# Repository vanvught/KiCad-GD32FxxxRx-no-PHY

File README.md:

[PayPal.Me Donate](https://paypal.me/AvanVught?locale.x=nl_NL)
-----------

# KiCad GD32F103R GD32F107R GD32F207R GD32F303R GD32F407R development board

This board can be used with the `GD32F103Rx`,  `GD32F303Rx` and the `GD32F107Rx` , `GD32F207Rx`, `GD32F407Rx` (Ethernet) MCU's. 

Please note that the crystal for the `GD32F107Rx`, `GD32F207Rx` and the `GD32F407Rx` is `25MHz` and the crystal for the `GD32F103Rx` and the  `GD32F303Rx` is `8MHz`.

The 2x13 header is pin compatible with the Orange Pi Zero and Raspberry Pi boards. 

Note: The BOM is for the GD32F407RE.
ToDo: Add information for other supported MCU's.

Details -> [https://www.gd32-dmx.org/dev-board.html](https://www.gd32-dmx.org/dev-board.html)

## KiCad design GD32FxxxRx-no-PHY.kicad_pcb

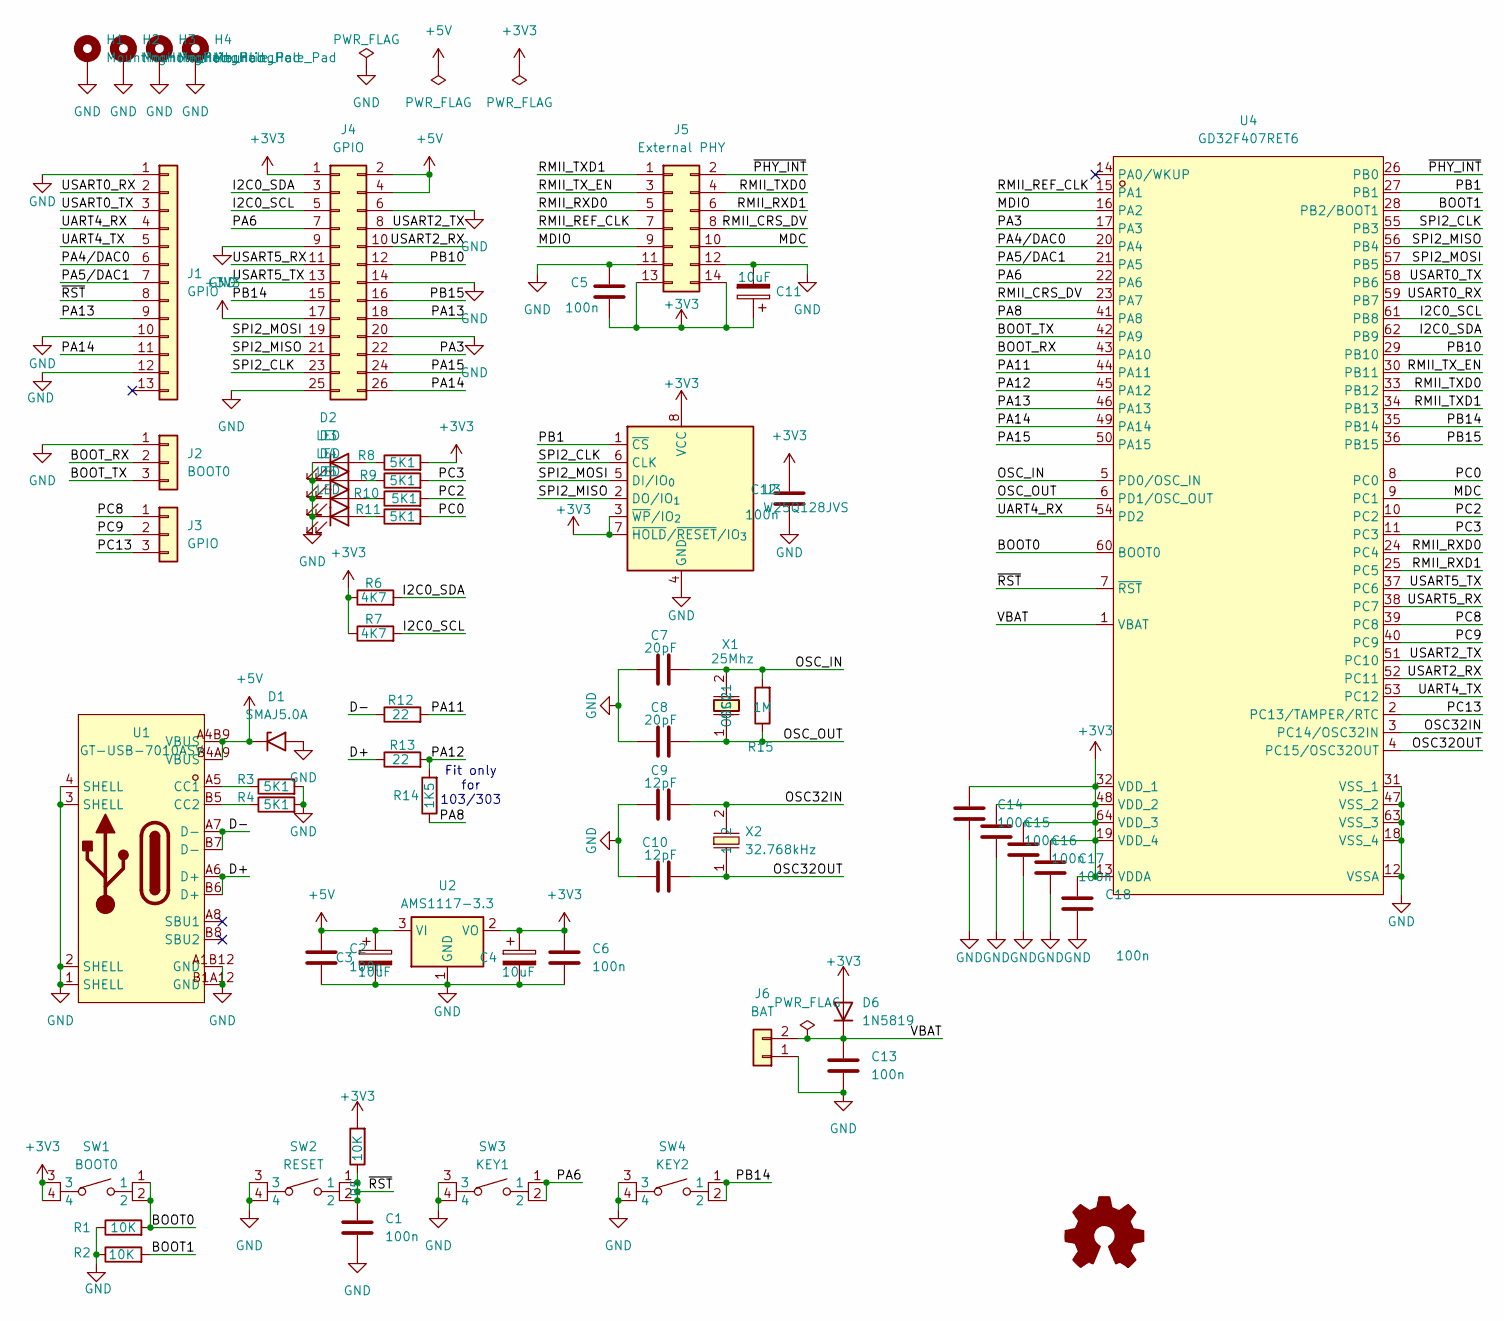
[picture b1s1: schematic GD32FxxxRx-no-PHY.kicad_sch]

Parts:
C1, C2, C5, C6, C12, C13, C14, C15, C16, C17, C18: 100n; C_0603_1608Metric; LCSC Part C14663
C3, C4, C11: 10uF; CP_EIA-3216-18_Kemet-A; LCSC Part C7171
C7, C8: 20pF; C_0603_1608Metric; LCSC Part C1648
C9, C10: 12pF; C_0603_1608Metric; LCSC Part C38523
D1: SMAJ5.0A; D_SMA; LCSC Part C113952
D2, D3, D4, D5: LED; LED_0805_2012Metric; LCSC Part C2297
D6: 1N5819; D_SOD-323; LCSC Part C48997863
H1, H2, H3, H4: MountingHole_Pad; MountingHole_2.7mm_M2.5_Pad
J1: GPIO; PinHeader_1x13_P2.54mm_Vertical
J2: BOOT0; PinHeader_1x03_P2.54mm_Vertical
J3: GPIO; PinHeader_1x03_P2.54mm_Vertical
J4: GPIO; PinHeader_2x13_P2.54mm_Vertical
J5: External PHY; PinSocket_2x07_P2.54mm_Horizontal
J6: BAT; PinHeader_1x02_P2.54mm_Vertical
R1, R2, R5: 10K; R_0603_1608Metric; LCSC Part C25804
R3, R4, R8, R9, R10, R11: 5K1; R_0603_1608Metric; LCSC Part C23186
R6, R7: 4K7; R_0603_1608Metric; LCSC Part C23162
R12, R13: 22; R_0603_1608Metric; LCSC Part C23345
R14: 1K5; R_0603_1608Metric; LCSC Part C22843
R15: 1M; R_0603_1608Metric; LCSC Part C22935
SW1: BOOT0; KEY-SMD_4P-L6.0-W6.0-P4.50-LS9.0; MPN PTS645SM43SMTR92LFS; LCSC Part C221880
SW2: RESET; KEY-SMD_4P-L6.0-W6.0-P4.50-LS9.0; MPN PTS645SM43SMTR92LFS; LCSC Part C221880
SW3: KEY1; KEY-SMD_4P-L6.0-W6.0-P4.50-LS9.0; MPN PTS645SM43SMTR92LFS; LCSC Part C221880
SW4: KEY2; KEY-SMD_4P-L6.0-W6.0-P4.50-LS9.0; MPN PTS645SM43SMTR92LFS; LCSC Part C221880
SYM1: Logo_Open_Hardware_Small; OSHW-Logo_5.7x6mm_SilkScreen
U1: GT-USB-7010ASV; USB-C-SMD_G-SWITCH_GT-USB-7010ASV; MPN GT-USB-7010ASV; LCSC Part C2988369
U2: AMS1117-3.3; SOT-223-3_TabPin2
U3: W25Q128JVS; SOIC-8_5.3x5.3mm_P1.27mm; LCSC Part C97521
U4: GD32F407RET6; LQFP-64_L10.0-W10.0-P0.50-LS12.0-BL; MPN GD32F407RET6; LCSC Part C2688748
X1: 25Mhz; HC-49S_L11.4-W4.8; MPN X49SM25MSD2SC; LCSC Part C14872
X2: 32.768kHz; FC-135R_L3.2-W1.5; MPN Q13FC13500004; LCSC Part C32346

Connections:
+3V3: C4.1, C5.2, C6.1, C11.1, C12.1, C14.1, C15.1, C16.1, C17.1, C18.1, D6.2 (A), J4.1, J4.17, J5.13, J5.14, R5.2, R6.1, R7.1, R8.2, SW1.3, SW1.4, U2.2 (VO), U3.3 (~WP/IO_{2}), U3.7 (~HOLD/~RESET/IO_{3}), U3.8 (VCC), U4.13 (VDDA), U4.19 (VDD_4), U4.32 (VDD_1), U4.48 (VDD_2), U4.64 (VDD_3)
+5V: C2.1, C3.1, D1.1 (A1), J4.2, J4.4, U1.A4B9 (VBUS), U1.B4A9 (VBUS), U2.3 (VI)
/BOOT0: R1.2, SW1.1, SW1.2, U4.60 (BOOT0)
/BOOT1: R2.2, U4.28 (PB2/BOOT1)
/BOOT_RX: J2.2, U4.43 (PA10)
/BOOT_TX: J2.3, U4.42 (PA9)
/D+: R13.1, U1.A6 (D+), U1.B6 (D+)
/D-: R12.1, U1.A7 (D-), U1.B7 (D-)
/I2C0_SCL: J4.5, R7.2, U4.61 (PB8)
/I2C0_SDA: J4.3, R6.2, U4.62 (PB9)
/MDC: J5.10, U4.9 (PC1)
/MDIO: J5.9, U4.16 (PA2)
/OSC32IN: C9.2, U4.3 (PC14/OSC32IN), X2.2
/OSC32OUT: C10.2, U4.4 (PC15/OSC32OUT), X2.1
/OSC_IN: C7.2, R15.2, U4.5 (PD0/OSC_IN), X1.2 (OSC2)
/OSC_OUT: C8.2, R15.1, U4.6 (PD1/OSC_OUT), X1.1 (OSC1)
/PA3: J4.22, U4.17 (PA3)
/PA4/DAC0: J1.6, U4.20 (PA4)
/PA5/DAC1: J1.7, U4.21 (PA5)
/PA6: J4.7, SW3.1, SW3.2, U4.22 (PA6)
/PA8: R14.1, U4.41 (PA8)
/PA11: R12.2, U4.44 (PA11)
/PA12: R13.2, R14.2, U4.45 (PA12)
/PA13: J1.9, J4.18, U4.46 (PA13)
/PA14: J1.11, J4.26, U4.49 (PA14)
/PA15: J4.24, U4.50 (PA15)
/PB1: U3.1 (~CS), U4.27 (PB1)
/PB10: J4.12, U4.29 (PB10)
/PB14: J4.15, SW4.1, SW4.2, U4.35 (PB14)
/PB15: J4.16, U4.36 (PB15)
/PC0: R11.2, U4.8 (PC0)
/PC2: R10.2, U4.10 (PC2)
/PC3: R9.2, U4.11 (PC3)
/PC8: J3.1, U4.39 (PC8)
/PC9: J3.2, U4.40 (PC9)
/PC13: J3.3, U4.2 (PC13/TAMPER/RTC)
/PHY_INT: J5.2, U4.26 (PB0)
/RMII_CRS_DV: J5.8, U4.23 (PA7)
/RMII_REF_CLK: J5.7, U4.15 (PA1)
/RMII_RXD0: J5.5, U4.24 (PC4)
/RMII_RXD1: J5.6, U4.25 (PC5)
/RMII_TXD0: J5.4, U4.33 (PB12)
/RMII_TXD1: J5.1, U4.34 (PB13)
/RMII_TX_EN: J5.3, U4.30 (PB11)
/SPI2_CLK: J4.23, U3.6 (CLK), U4.55 (PB3)
/SPI2_MISO: J4.21, U3.2 (DO/IO_{1}), U4.56 (PB4)
/SPI2_MOSI: J4.19, U3.5 (DI/IO_{0}), U4.57 (PB5)
/UART4_RX: J1.4, U4.54 (PD2)
/UART4_TX: J1.5, U4.53 (PC12)
/USART0_RX: J1.2, U4.59 (PB7)
/USART0_TX: J1.3, U4.58 (PB6)
/USART2_RX: J4.10, U4.52 (PC11)
/USART2_TX: J4.8, U4.51 (PC10)
/USART5_RX: J4.11, U4.38 (PC7)
/USART5_TX: J4.13, U4.37 (PC6)
/VBAT: C13.1, D6.1 (K), J6.2, U4.1 (VBAT)
/~RST: C1.1, J1.8, R5.1, SW2.1, SW2.2, U4.7 (~RST)
GND: C1.2, C2.2, C3.2, C4.2, C5.1, C6.2, C7.1, C8.1, C9.1, C10.1, C11.2, C12.2, C13.2, C14.2, C15.2, C16.2, C17.2, C18.2, D1.2 (A2), D2.1 (K), D3.1 (K), D4.1 (K), D5.1 (K), H1.1 (1_1), H2.1 (1_1), H3.1 (1_1), H4.1 (1_1), J1.1, J1.10, J1.12, J2.1, J4.6, J4.9, J4.14, J4.20, J4.25, J5.11, J5.12, J6.1, R1.1, R2.1, R3.2, R4.2, SW2.3, SW2.4, SW3.3, SW3.4, SW4.3, SW4.4, U1.1 (SHELL), U1.2 (SHELL), U1.3 (SHELL), U1.4 (SHELL), U1.A1B12 (GND), U1.B1A12 (GND), U2.1 (GND), U3.4 (GND), U4.12 (VSSA), U4.18 (VSS_4), U4.31 (VSS_1), U4.47 (VSS_2), U4.63 (VSS_3)
unnamed: D2.2 (A), R8.1
unnamed: D3.2 (A), R9.1
unnamed: D4.2 (A), R10.1
unnamed: D5.2 (A), R11.1
unnamed: R3.1, U1.A5 (CC1)
unnamed: R4.1, U1.B5 (CC2)

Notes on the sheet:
Fit only for 103/303

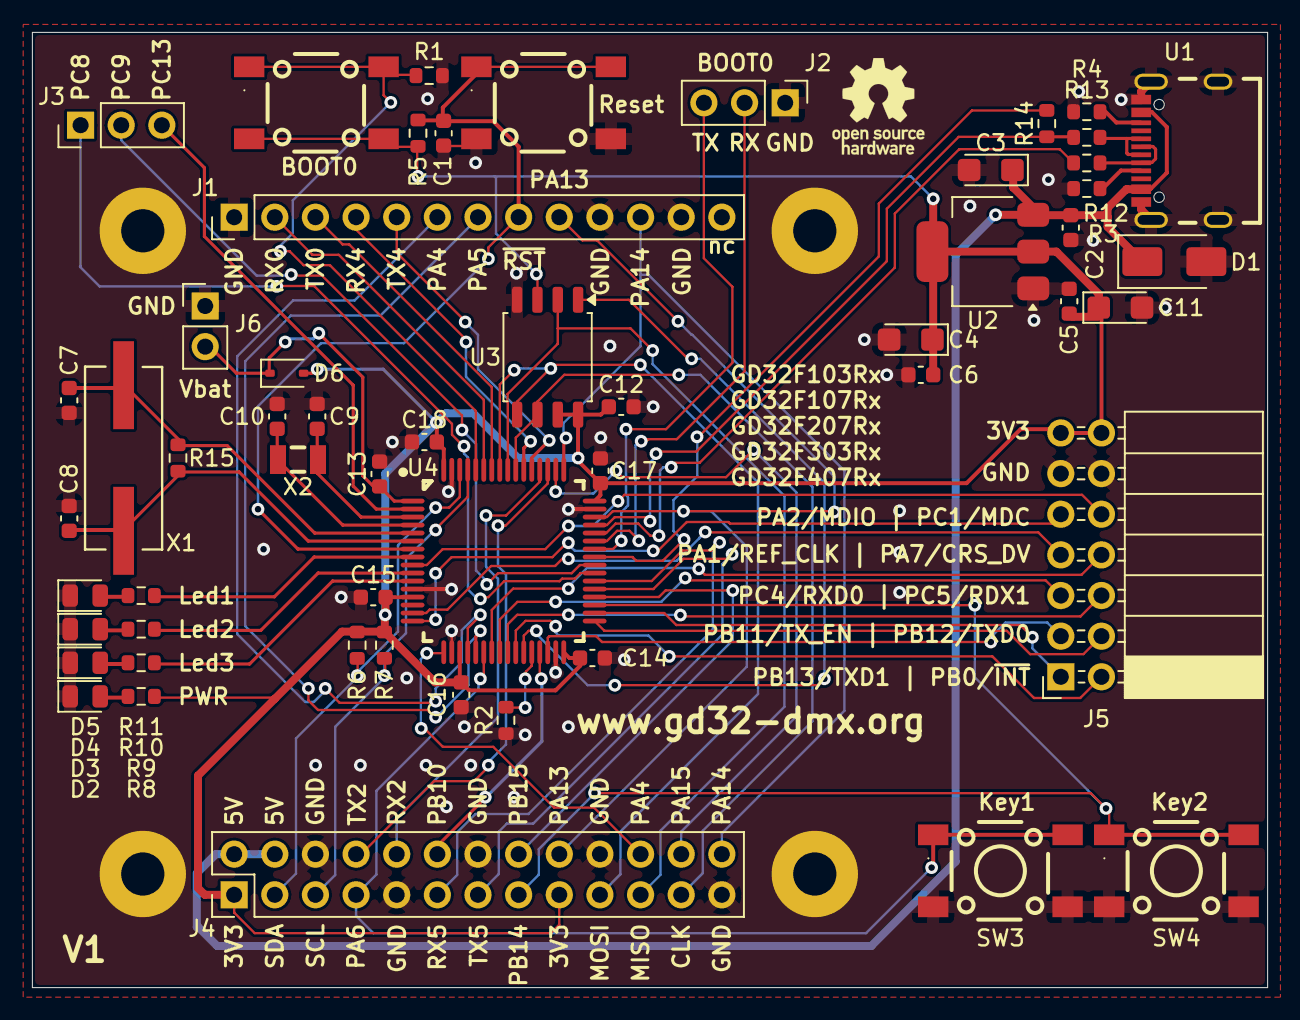
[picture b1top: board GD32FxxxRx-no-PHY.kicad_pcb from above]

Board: 2 copper layers, 77.2 x 59.7 mm, 60 parts (0 on the bottom side), 64 nets.

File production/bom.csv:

Designator,Footprint,Quantity,Value,LCSC Part #
"C1, C12, C13, C14, C15, C16, C17, C18, C2, C5, C6",0603,11,100n,C14663
"C10, C9",0603,2,12pF,C38523 
"C11, C3, C4",CP_EIA-3216-18_Kemet-A,3,10uF,C7171
"C7, C8",0603,2,20pF,C1648
D1,D_SMA,1,SMAJ5.0A,C113952
"D2, D3, D4, D5",0805,4,LED,C2297
D6,D_SOD-323,1,1N5819,C48997863
"R1, R2, R5",0603,3,10K,C25804
"R10, R8, R9",0603,3,1K5,C22975
R11,0603,1,1K5,C22843
"R12, R13",0603,2,22,C23345
R15,0603,1,1M,C22935
"R3, R4",0603,2,5K1,C23186
"R6, R7",0603,2,4K7,C23162
SW1,KEY-SMD_4P-L6.0-W6.0-P4.50-LS9.0,1,BOOT0,C221880
SW2,KEY-SMD_4P-L6.0-W6.0-P4.50-LS9.0,1,RESET,C221880
SW3,KEY-SMD_4P-L6.0-W6.0-P4.50-LS9.0,1,KEY1,C221880
SW4,KEY-SMD_4P-L6.0-W6.0-P4.50-LS9.0,1,KEY2,C221880
U1,USB-C-SMD_G-SWITCH_GT-USB-7010ASV,1,GT-USB-7010ASV,C2988369
U2,SOT-223-3_TabPin2,1,AMS1117-3.3,
U3,SOIC-8_5.3x5.3mm_P1.27mm,1,W25Q128JVS,C97521
U4,LQFP-64_L10.0-W10.0-P0.50-LS12.0-BL,1,GD32F407RET6,C2688748
X1,HC-49S_L11.4-W4.8,1,25Mhz,C14872
X2,FC-135R_L3.2-W1.5,1,32.768kHz,C32346
